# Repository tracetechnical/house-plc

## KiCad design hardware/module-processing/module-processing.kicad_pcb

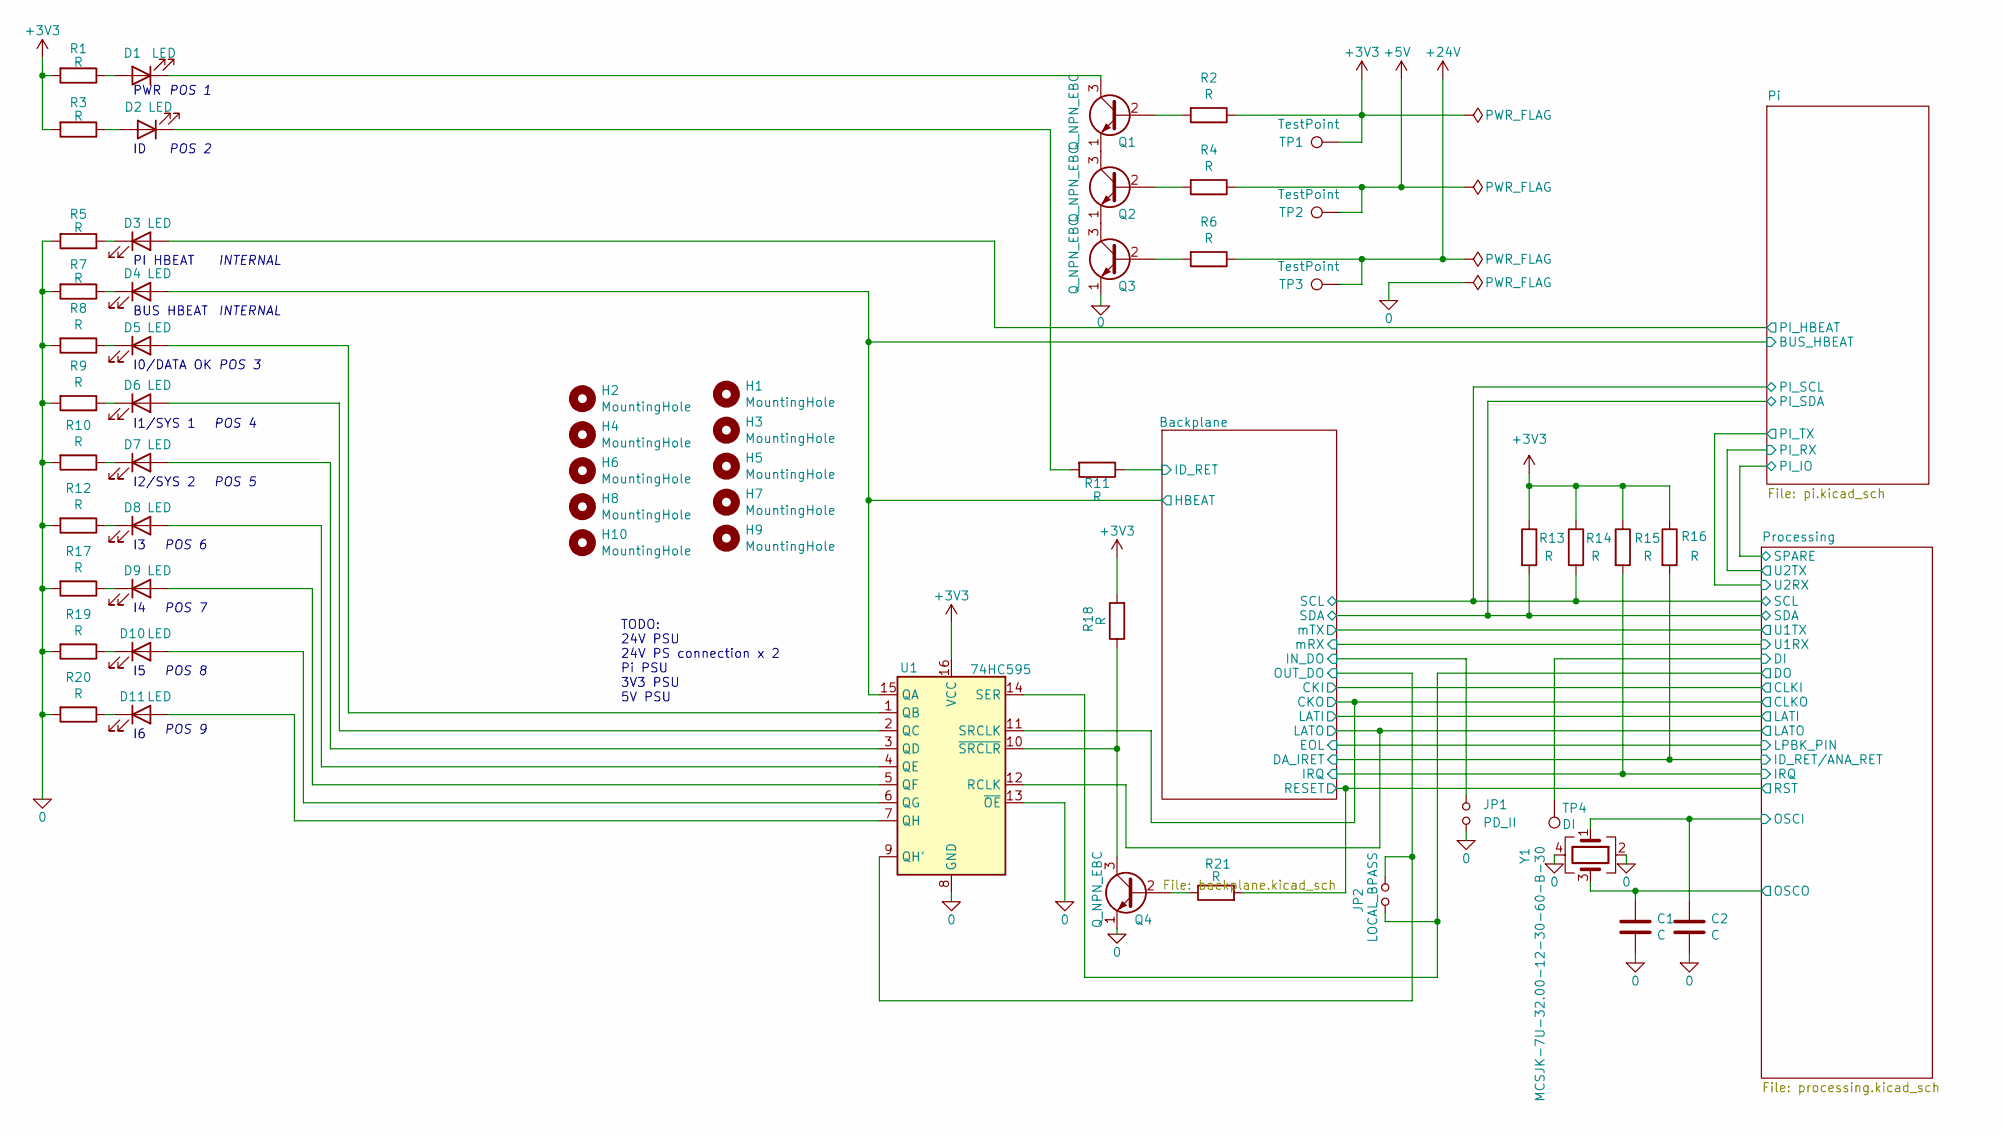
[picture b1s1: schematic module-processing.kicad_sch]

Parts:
C1, C2: C; C_0805_2012Metric_Pad1.18x1.45mm_HandSolder
D1, D2, D3, D4, D5, D6, D7, D8, D9, D10, D11: LED; LED_0603_1608Metric_Pad1.05x0.95mm_HandSolder
H1, H2, H3, H4, H5, H6, H7, H8, H9, H10: MountingHole; MountingHole_2.5mm
JP1: PD_II; SolderJumper-2_P1.3mm_Open_Pad1.0x1.5mm
JP2: LOCAL_BPASS; SolderJumper-2_P1.3mm_Open_Pad1.0x1.5mm
Q1, Q2, Q3, Q4: Q_NPN_EBC; SOT-23
R1, R2, R3, R4, R5, R6, R7, R8, R9, R10, R11, R12, R13, R14, R15, R16, R17, R18, R19, R20, R21: R; R_0805_2012Metric_Pad1.20x1.40mm_HandSolder
TP1, TP2, TP3: TestPoint; TestPoint_Pad_D2.0mm
TP4: DI; TestPoint_Pad_D2.0mm
U1: 74HC595; SOIC-16_3.9x9.9mm_P1.27mm
Y1: MCSJK-7U-32.00-12-30-60-B-30; Crystal_SMD_3225-4Pin_3.2x2.5mm_HandSoldering

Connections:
0: C1.2, C2.2, JP1.1, Q3.1 (E), Q4.1 (E), R5.2, R7.2, R8.2, R9.2, R10.2, R12.2, R17.2, R19.2, R20.2, U1.8 (GND), U1.13 (~OE), Y1.2, Y1.4; also elsewhere on the board
+3V3: R1.2, R2.1, R3.2, R13.1, R14.1, R15.1, R16.1, R18.2, TP1.1, U1.16 (VCC); also elsewhere on the board
+5V: R4.1, TP2.1; also elsewhere on the board
+24V: R6.1, TP3.1
/Backplane/CKO: U1.11 (SRCLK); also elsewhere on the board
/Backplane/DA_IRET: R16.2; also elsewhere on the board
/Backplane/HBEAT: D4.2 (A), U1.15 (QA); also elsewhere on the board
/Backplane/ID_RET: R11.1; also elsewhere on the board
/Backplane/IN_DO: JP1.2; also elsewhere on the board
/Backplane/IRQ: R15.2; also elsewhere on the board
/Backplane/LATO: U1.12 (RCLK); also elsewhere on the board
/Backplane/OUT_DO: JP2.2, U1.9 (QH'); also elsewhere on the board
/Backplane/RESET: R21.2; also elsewhere on the board
/Backplane/SCL: R14.2; also elsewhere on the board
/Backplane/SDA: R13.2; also elsewhere on the board
/Pi/PI_HBEAT: D3.2 (A); also elsewhere on the board
/Processing/DI: TP4.1; also elsewhere on the board
/Processing/DO: JP2.1, U1.14 (SER); also elsewhere on the board
/Processing/OSCI: C2.1, Y1.1; also elsewhere on the board
/Processing/OSCO: C1.1, Y1.3; also elsewhere on the board
unnamed: D1.1 (K), Q1.3 (C)
unnamed: D1.2 (A), R1.1
unnamed: D2.1 (K), R11.2
unnamed: D2.2 (A), R3.1
unnamed: D3.1 (K), R5.1
unnamed: D4.1 (K), R7.1
unnamed: D5.1 (K), R8.1
unnamed: D5.2 (A), U1.1 (QB)
unnamed: D6.1 (K), R9.1
unnamed: D6.2 (A), U1.2 (QC)
unnamed: D7.1 (K), R10.1
unnamed: D7.2 (A), U1.3 (QD)
unnamed: D8.1 (K), R12.1
unnamed: D8.2 (A), U1.4 (QE)
unnamed: D9.1 (K), R17.1
unnamed: D9.2 (A), U1.5 (QF)
unnamed: D10.1 (K), R19.1
unnamed: D10.2 (A), U1.6 (QG)
unnamed: D11.1 (K), R20.1
unnamed: D11.2 (A), U1.7 (QH)
unnamed: Q1.1 (E), Q2.3 (C)
unnamed: Q1.2 (B), R2.2
unnamed: Q2.1 (E), Q3.3 (C)
unnamed: Q2.2 (B), R4.2
unnamed: Q3.2 (B), R6.2
unnamed: Q4.2 (B), R21.1
unnamed: Q4.3 (C), R18.1, U1.10 (~SRCLR)

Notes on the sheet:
POS 5
POS 6
POS 8
I1/SYS 1
INTERNAL
TODO: 24V PSU 24V PS connection x 2 Pi PSU 3V3 PSU 5V PSU
I2/SYS 2
POS 3
POS 2
POS 9
I0/DATA OK
PWR
POS 1
BUS HBEAT
PI HBEAT
POS 4
POS 7

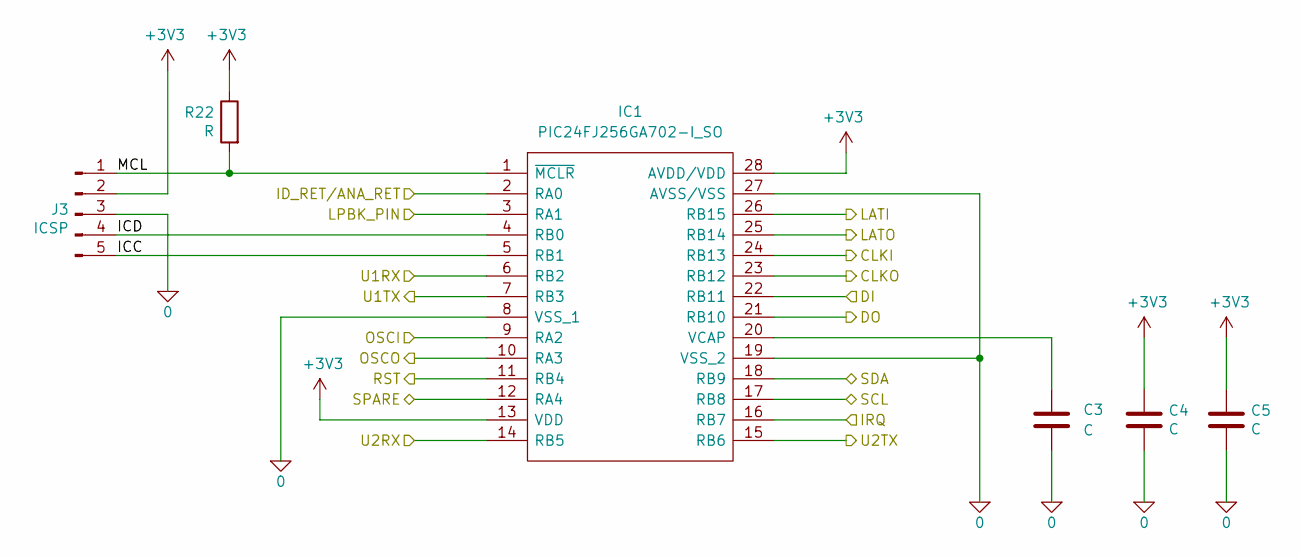
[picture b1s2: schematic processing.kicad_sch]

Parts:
C3, C4, C5: C; C_0805_2012Metric_Pad1.18x1.45mm_HandSolder
IC1: PIC24FJ256GA702-I_SO; SOIC-28W_7.5x17.9mm_P1.27mm; Manufacturer_Part_Number PIC24FJ256GA702-I/SO; Mouser Part Number 579-24FJ256GA702ISO
J3: ICSP; Molex_KK-254_AE-6410-05A_1x05_P2.54mm_Vertical
R22: R; R_0805_2012Metric_Pad1.20x1.40mm_HandSolder

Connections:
0: C3.2, C4.2, C5.2, IC1.8 (VSS_1), IC1.19 (VSS_2), IC1.27 (AVSS/VSS), J3.3; also elsewhere on the board
+3V3: C4.1, C5.1, IC1.13 (VDD), IC1.28 (AVDD/VDD), J3.2, R22.1; also elsewhere on the board
/Backplane/CKI: IC1.24 (RB13); also elsewhere on the board
/Backplane/CKO: IC1.23 (RB12); also elsewhere on the board
/Backplane/DA_IRET: IC1.2 (RA0); also elsewhere on the board
/Backplane/EOL: IC1.3 (RA1); also elsewhere on the board
/Backplane/IRQ: IC1.16 (RB7); also elsewhere on the board
/Backplane/LATI: IC1.26 (RB15); also elsewhere on the board
/Backplane/LATO: IC1.25 (RB14); also elsewhere on the board
/Backplane/RESET: IC1.11 (RB4); also elsewhere on the board
/Backplane/SCL: IC1.17 (RB8); also elsewhere on the board
/Backplane/SDA: IC1.18 (RB9); also elsewhere on the board
/Backplane/mRX: IC1.6 (RB2); also elsewhere on the board
/Backplane/mTX: IC1.7 (RB3); also elsewhere on the board
/Pi/PI_IO: IC1.12 (RA4); also elsewhere on the board
/Pi/PI_RX: IC1.15 (RB6); also elsewhere on the board
/Pi/PI_TX: IC1.14 (RB5); also elsewhere on the board
/Processing/DI: IC1.22 (RB11); also elsewhere on the board
/Processing/DO: IC1.21 (RB10); also elsewhere on the board
/Processing/ICC: IC1.5 (RB1), J3.5
/Processing/ICD: IC1.4 (RB0), J3.4
/Processing/MCL: IC1.1 (~MCLR), J3.1, R22.2
/Processing/OSCI: IC1.9 (RA2); also elsewhere on the board
/Processing/OSCO: IC1.10 (RA3); also elsewhere on the board
unnamed: C3.1, IC1.20 (VCAP)

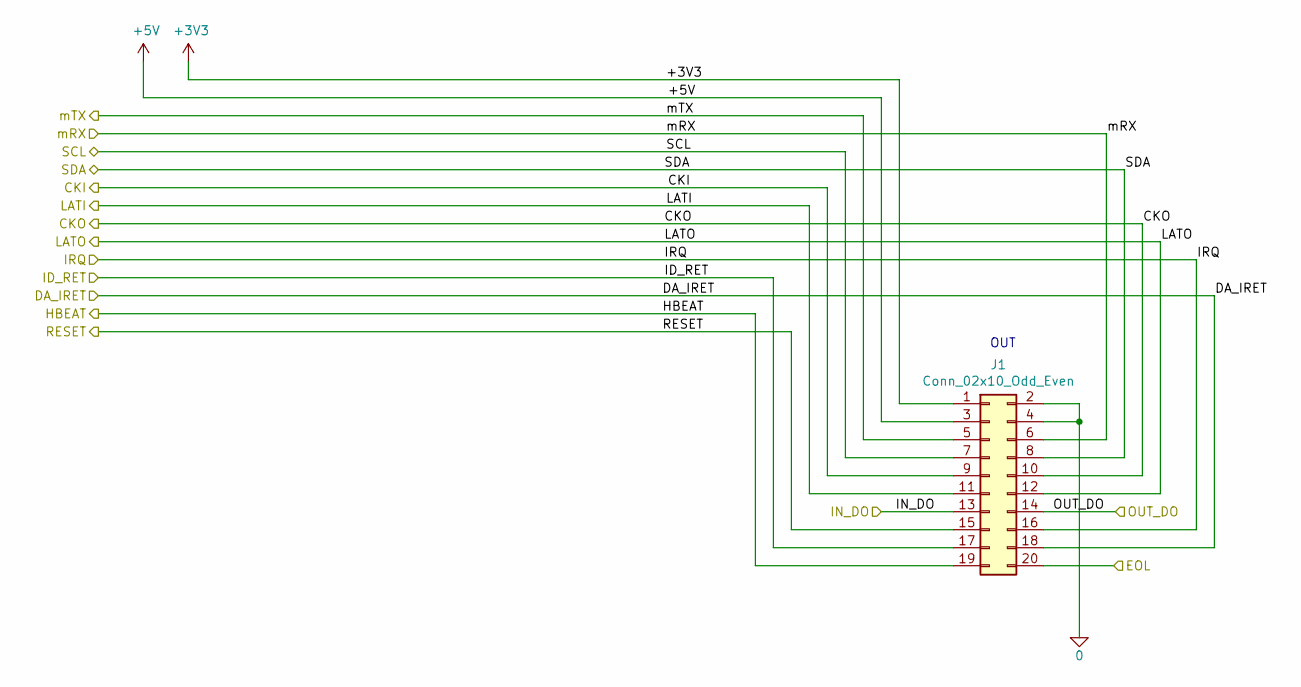
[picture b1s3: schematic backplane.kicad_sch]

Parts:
J1: Conn_02x10_Odd_Even; IDC-Header_2x10_P2.54mm_Vertical

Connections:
0: J1.2, J1.4; also elsewhere on the board
+3V3: J1.1; also elsewhere on the board
+5V: J1.3; also elsewhere on the board
/Backplane/CKI: J1.9; also elsewhere on the board
/Backplane/CKO: J1.10; also elsewhere on the board
/Backplane/DA_IRET: J1.18; also elsewhere on the board
/Backplane/EOL: J1.20; also elsewhere on the board
/Backplane/HBEAT: J1.19; also elsewhere on the board
/Backplane/ID_RET: J1.17; also elsewhere on the board
/Backplane/IN_DO: J1.13; also elsewhere on the board
/Backplane/IRQ: J1.16; also elsewhere on the board
/Backplane/LATI: J1.11; also elsewhere on the board
/Backplane/LATO: J1.12; also elsewhere on the board
/Backplane/OUT_DO: J1.14; also elsewhere on the board
/Backplane/RESET: J1.15; also elsewhere on the board
/Backplane/SCL: J1.7; also elsewhere on the board
/Backplane/SDA: J1.8; also elsewhere on the board
/Backplane/mRX: J1.6; also elsewhere on the board
/Backplane/mTX: J1.5; also elsewhere on the board

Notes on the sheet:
OUT

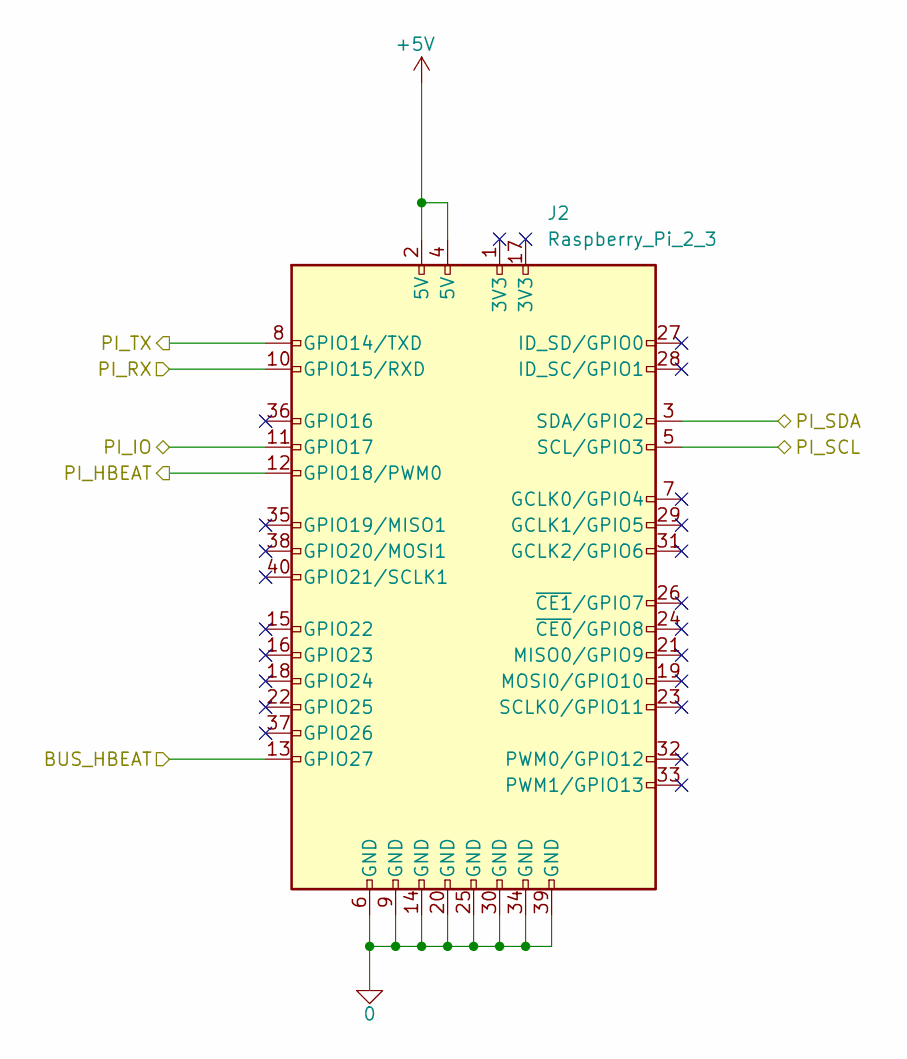
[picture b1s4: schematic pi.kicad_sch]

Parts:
J2: Raspberry_Pi_2_3; Raspberry_Pi_Zero_Socketed_THT_FaceDown_MountingHoles

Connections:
0: J2.6 (GND), J2.9 (GND), J2.14 (GND), J2.20 (GND), J2.25 (GND), J2.30 (GND), J2.34 (GND), J2.39 (GND); also elsewhere on the board
+5V: J2.2 (5V), J2.4 (5V); also elsewhere on the board
/Backplane/HBEAT: J2.13 (GPIO27); also elsewhere on the board
/Backplane/SCL: J2.5 (SCL/GPIO3); also elsewhere on the board
/Backplane/SDA: J2.3 (SDA/GPIO2); also elsewhere on the board
/Pi/PI_HBEAT: J2.12 (GPIO18/PWM0); also elsewhere on the board
/Pi/PI_IO: J2.11 (GPIO17); also elsewhere on the board
/Pi/PI_RX: J2.10 (GPIO15/RXD); also elsewhere on the board
/Pi/PI_TX: J2.8 (GPIO14/TXD); also elsewhere on the board

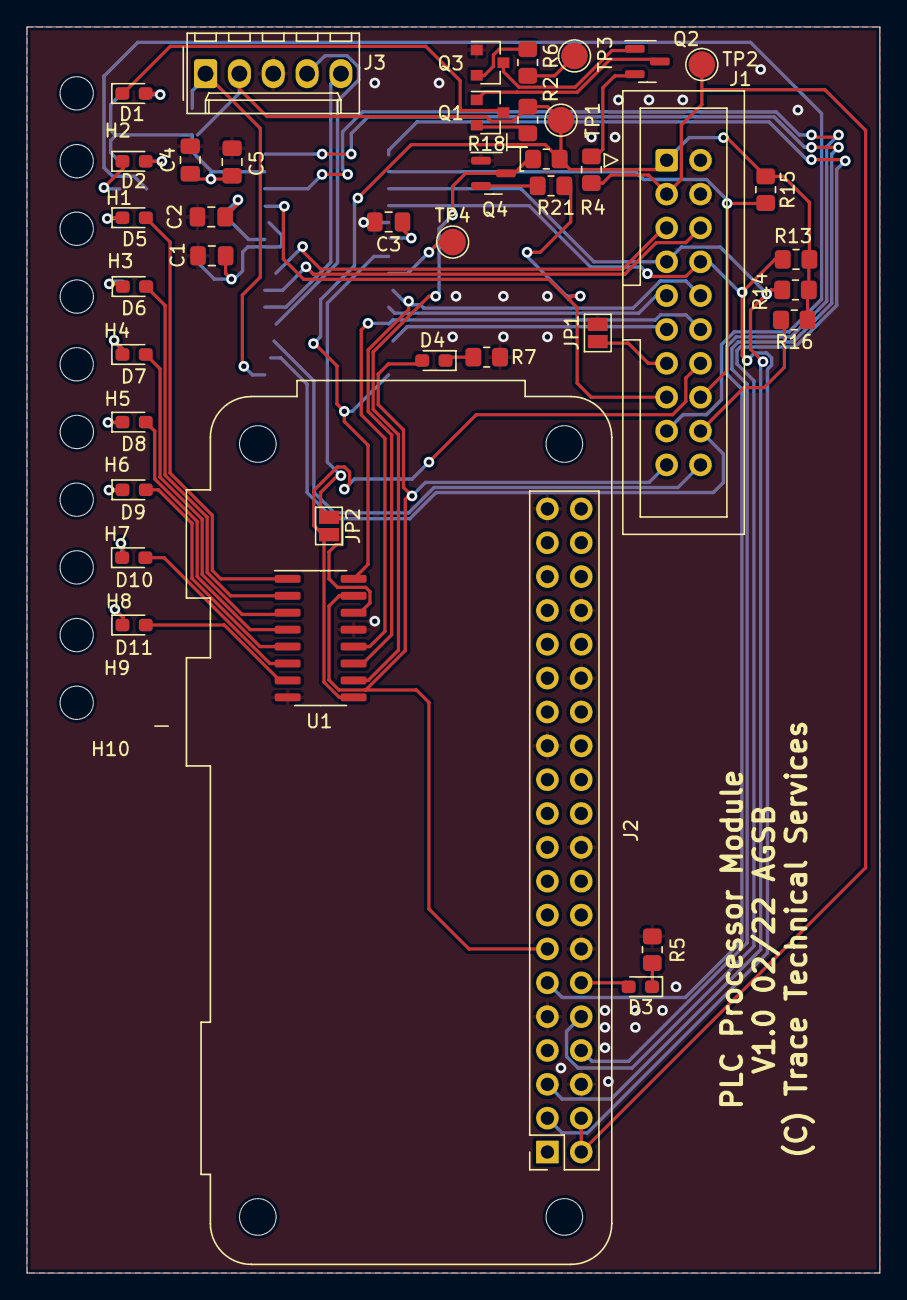
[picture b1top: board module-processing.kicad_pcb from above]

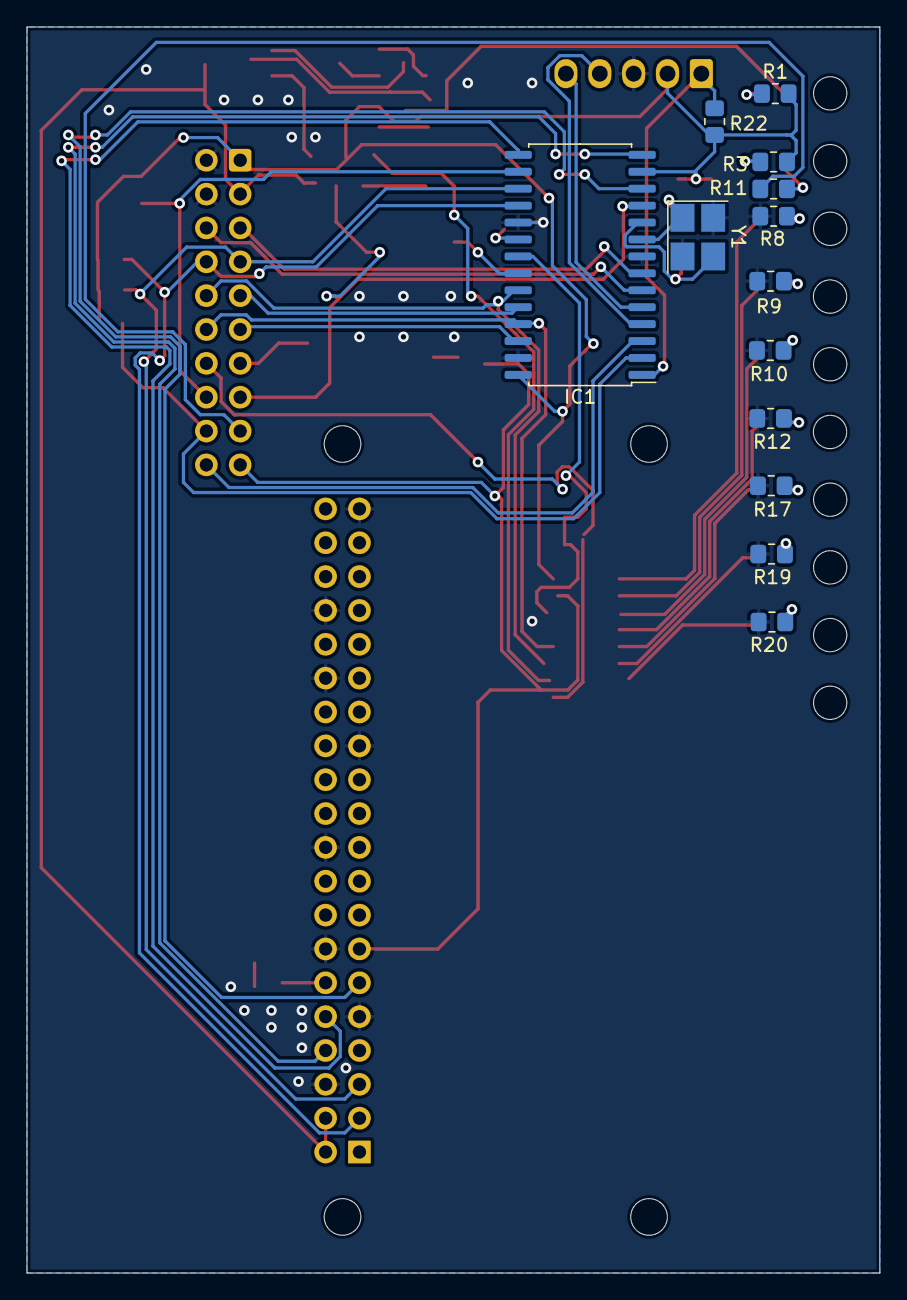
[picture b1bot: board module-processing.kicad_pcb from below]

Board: 2 copper layers, 64.0 x 93.5 mm, 64 parts (13 on the bottom side), 59 nets.

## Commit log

2022-02-13 feat: initial commit (kicad 6.0)
2022-02-13 fix: move pi to sensible position; chore: tidy and check
2022-02-13 feat: add gerbers processor; feat: add schema pdf
2022-02-13 feat: add labels to io pcb; feat: add labels to cpu pcb
2022-02-14 feat: add protection to bus conns io
